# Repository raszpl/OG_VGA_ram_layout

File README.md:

Quick and dirty investigation into original 1987 IBM Personal System/2 Display Adapter aka very first VGA card https://www.minuszerodegrees.net/video/IBM%20Announcement%20Letter%20187-054.txt https://upload.wikimedia.org/wikipedia/commons/3/3f/IBM_VGA_graphics_card.jpg

My original assumption was that IBM "simply" consolidated EGA CRT Controller (CRTC), Timing Sequencer (TS), Attribute Controller (ATC)
and two GDCs into one huge ass ~200 pin LSI and called it a day. This would mean virtual 4 banks of 64KB physically organized as one big 32bit pool.
EGA implementation is documented in IBMs original diagrams and Tube Times fantastic reversed pcb https://github.com/schlae/EGACard.
Original EGA used two LSI GDCs (Graphics Data Controllers) each controlling 4 ram chips and 16bit of data bus giving it combined 32bit data bus.

Tracing visible tracks confirms it. Original IBM VGA implementations didnt differ logically from EGA.

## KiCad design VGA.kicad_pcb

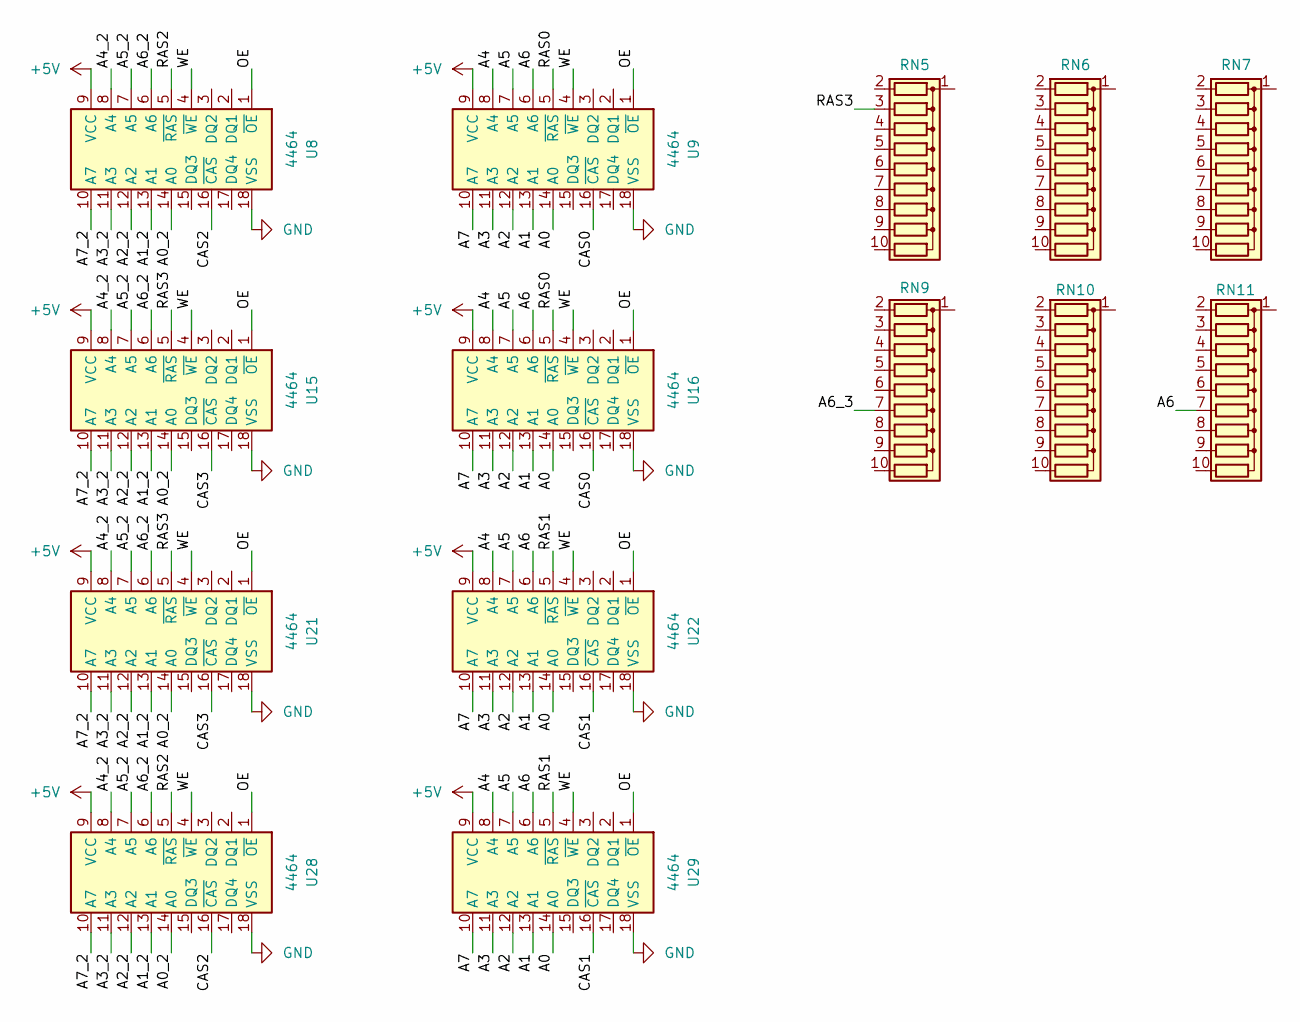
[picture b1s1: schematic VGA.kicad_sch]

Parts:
RN5, RN6, RN7, RN9, RN10, RN11: R_Network10; R_Array_SIP10
U8, U9, U15, U16, U21, U22, U28, U29: 4464; DIP-18_W7.62mm

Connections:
+5V: U8.9 (VCC), U9.9 (VCC), U15.9 (VCC), U16.9 (VCC), U21.9 (VCC), U22.9 (VCC), U28.9 (VCC), U29.9 (VCC)
/A0: U9.14 (A0), U16.14 (A0), U22.14 (A0), U29.14 (A0)
/A0_2: U8.14 (A0), U15.14 (A0), U21.14 (A0), U28.14 (A0)
/A1: U9.13 (A1), U16.13 (A1), U22.13 (A1), U29.13 (A1)
/A1_2: U8.13 (A1), U15.13 (A1), U21.13 (A1), U28.13 (A1)
/A2: U9.12 (A2), U16.12 (A2), U22.12 (A2), U29.12 (A2)
/A2_2: U8.12 (A2), U15.12 (A2), U21.12 (A2), U28.12 (A2)
/A3: U9.11 (A3), U16.11 (A3), U22.11 (A3), U29.11 (A3)
/A3_2: U8.11 (A3), U15.11 (A3), U21.11 (A3), U28.11 (A3)
/A4: U9.8 (A4), U16.8 (A4), U22.8 (A4), U29.8 (A4)
/A4_2: U8.8 (A4), U15.8 (A4), U21.8 (A4), U28.8 (A4)
/A5: U9.7 (A5), U16.7 (A5), U22.7 (A5), U29.7 (A5)
/A5_2: U8.7 (A5), U15.7 (A5), U21.7 (A5), U28.7 (A5)
/A6: RN11.7 (R6_7), U9.6 (A6), U16.6 (A6), U22.6 (A6), U29.6 (A6)
/A6_2: U8.6 (A6), U15.6 (A6), U21.6 (A6), U28.6 (A6)
/A6_3: RN9.7 (R6_7)
/A7: U9.10 (A7), U16.10 (A7), U22.10 (A7), U29.10 (A7)
/A7_2: U8.10 (A7), U15.10 (A7), U21.10 (A7), U28.10 (A7)
/CAS0: U9.16 (~CAS), U16.16 (~CAS)
/CAS1: U22.16 (~CAS), U29.16 (~CAS)
/CAS2: U8.16 (~CAS), U28.16 (~CAS)
/CAS3: U15.16 (~CAS), U21.16 (~CAS)
/OE: U8.1 (~OE), U9.1 (~OE), U15.1 (~OE), U16.1 (~OE), U21.1 (~OE), U22.1 (~OE), U28.1 (~OE), U29.1 (~OE)
/RAS0: U9.5 (~RAS), U16.5 (~RAS)
/RAS1: U22.5 (~RAS), U29.5 (~RAS)
/RAS2: U8.5 (~RAS), U28.5 (~RAS)
/RAS3: RN5.3 (R2_3), U15.5 (~RAS), U21.5 (~RAS)
/WE: U8.4 (~WE), U9.4 (~WE), U15.4 (~WE), U16.4 (~WE), U21.4 (~WE), U22.4 (~WE), U28.4 (~WE), U29.4 (~WE)
GND: U8.18 (VSS), U9.18 (VSS), U15.18 (VSS), U16.18 (VSS), U21.18 (VSS), U22.18 (VSS), U28.18 (VSS), U29.18 (VSS)

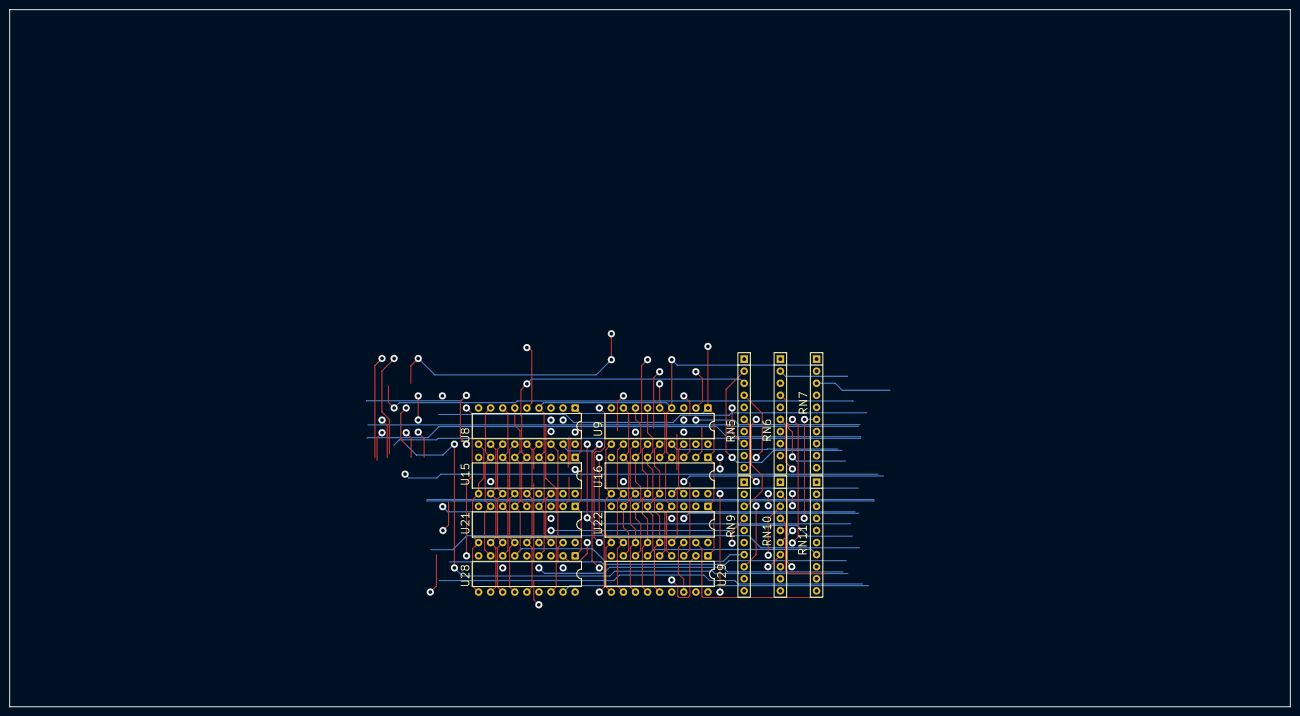
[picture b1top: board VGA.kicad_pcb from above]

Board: 4 copper layers, 269.5 x 146.7 mm, 14 parts (0 on the bottom side), 28 nets.

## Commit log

2026-05-19 initial re
